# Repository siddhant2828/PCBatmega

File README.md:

PCB atmega328
In this project I have design a customized PCB for arduino board using EAGLE IDE.
The board files , schematic file and PNJ image.

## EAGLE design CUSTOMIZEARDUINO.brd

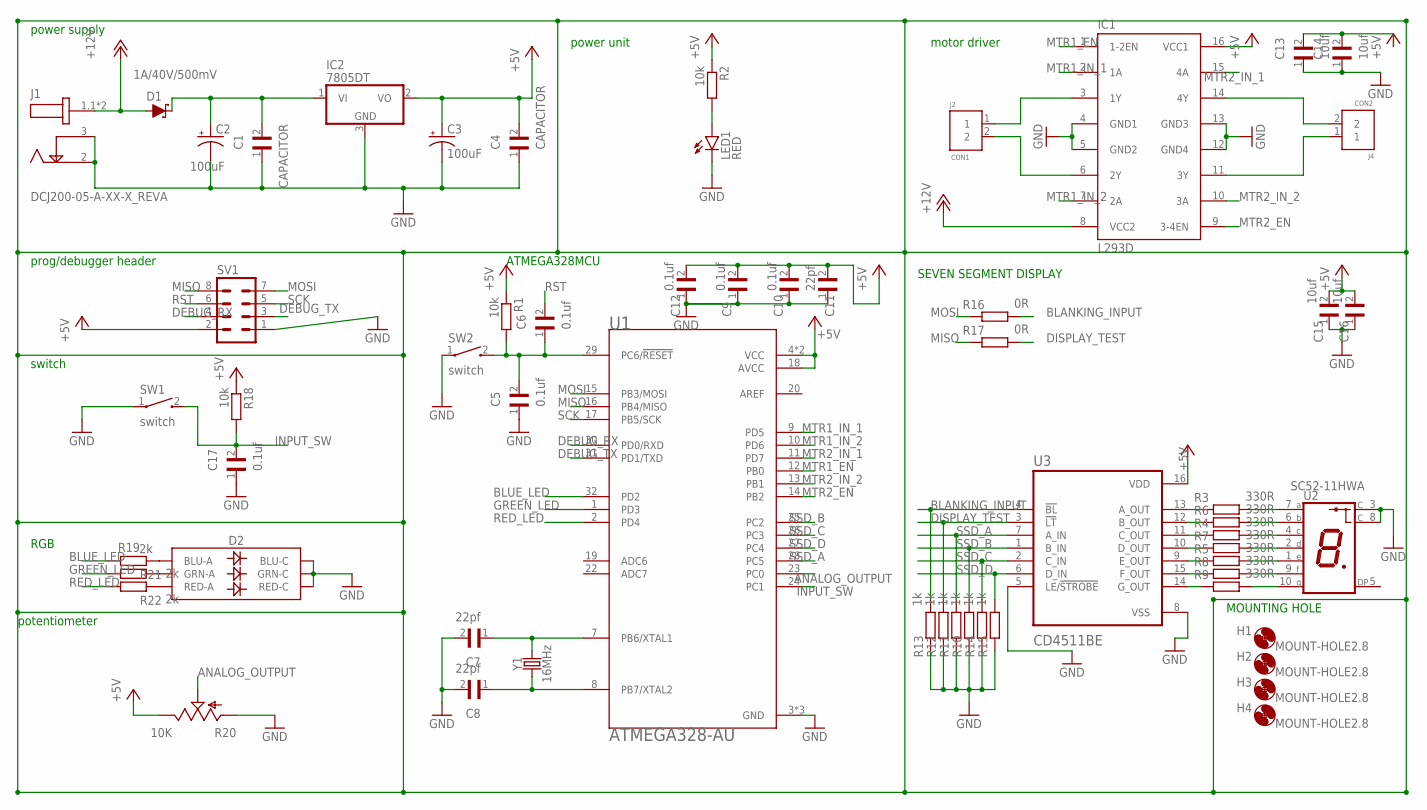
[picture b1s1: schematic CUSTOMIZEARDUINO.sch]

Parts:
C1, C4: CAPACITOR; C0603
C2, C3: 100uF; CPOL-RADIAL-2.5MM-6.5MM
C5, C6, C9, C10, C12, C17: 0.1uf; C0603
C7, C8, C11: 22pf; C0603
C13, C14, C15, C16: 10uf; C0603
D1: 1A/40V/500mV; SMA-DIODE
D2: LED-RGBBRG; LED-TRICOLOR-5050
H1, H2, H3, H4: MOUNT-HOLE2.8; 2,8
IC1: L293D; DIL16
IC2: 7805DT; TO252
J1: DCJ200-05-A-XX-X_REVA; GCT_DCJ200-05-A-XX-X_REVA
J2: CON1; CONN_282836-2
J4: CON2; CONN_282836-2
LED1: RED; SMARTLED-TTW
R1, R2, R18: 10k; R0603
R3, R4, R5, R6, R7, R8, R9: 330R; R0603
R10, R11, R12, R13, R14, R15: 1k; R0603
R16, R17: 0R; R0603
R19, R21, R22: 2k; R0603
R20: 10K; S64W
SV1: MA04-2
SW1, SW2: switch; SW_1437566-3
U1: ATMEGA328-AU; QFP80P900X900X120-32N
U2: SC52-11HWA; LED_SC52-11HWA
U3: CD4511BE; DIP794W45P254L1969H508Q16
Y1: 16MHz; HC49US

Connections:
+5V: C3.1 (+), C4.2, C9.2, C10.2, C11.2, C12.2, C13.2, C14.2, C15.2, C16.2, IC1.16 (VCC1), IC2.2 (VO), R1.1, R2.1, R18.1, R20.E, SV1.2, U1.4 (VCC), U1.6 (VCC), U1.18 (AVCC), U3.16 (VDD)
+12V: D1.A, IC1.8 (VCC2), J1.1.1 (1), J1.1.2 (1)
ANALOG_OUTPUT: R20.S, U1.23 (PC0)
BLANKING_INPUT: R13.2, R16.2, U3.4 (!BL)
BLUE_LED: D2.6 (BLU-A), R19.1, R19.2, U1.32 (PD2)
DEBUG_RX: SV1.4, U1.30 (PD0/RXD)
DEBUG_TX: SV1.3, U1.31 (PD1/TXD)
DISPLAY_TEST: R12.2, R17.2, U3.3 (!LT)
GND: C1.1, C2.2 (-), C3.2 (-), C4.1, C5.1, C7.2, C8.2, C9.1, C10.1, C11.1, C12.1, C13.1, C14.1, C15.1, C16.1, C17.1, D2.1 (BLU-C), D2.2 (RED-C), D2.3 (GRN-C), IC1.4 (GND1), IC1.5 (GND2), IC1.12 (GND4), IC1.13 (GND3), IC2.3 (GND), J1.2, J1.3, LED1.C@1 (C), R10.1, R11.1, R12.1, R13.1, R14.1, R15.1, R20.A, SV1.1, SW1.1, SW2.1, U1.3 (GND), U1.5 (GND), U1.21 (GND), U2.3 (C), U2.8 (C), U3.5 (LE/!STROBE), U3.8 (VSS)
GREEN_LED: R21.1, U1.1 (PD3)
INPUT_SW: C17.2, R18.2, SW1.2, U1.24 (PC1)
MISO: R17.1, SV1.8, U1.16 (PB4/MISO)
MOSI: R16.1, SV1.7, U1.15 (PB3/MOSI)
MTR1_EN: IC1.1 (1-2EN), U1.12 (PB0)
MTR1_IN_1: IC1.2 (1A), U1.9 (PD5)
MTR1_IN_2: IC1.7 (2A), U1.10 (PD6)
MTR2_EN: IC1.9 (3-4EN), U1.14 (PB2)
MTR2_IN_1: IC1.15 (4A), U1.11 (PD7)
MTR2_IN_2: IC1.10 (3A), U1.13 (PB1)
unnamed: C1.2, C2.1 (+), D1.C, IC2.1 (VI)
unnamed: C5.2, C6.1, R1.2, SW2.2, U1.29 (PC6/!RESET)
unnamed: C7.1, U1.7 (PB6/XTAL1), Y1.2
unnamed: C8.1, U1.8 (PB7/XTAL2), Y1.1
unnamed: LED1.A@1 (A), R2.2
unnamed: R3.1, U3.13 (A_OUT)
unnamed: R6.1, U3.12 (B_OUT)
unnamed: R4.1, U3.11 (C_OUT)
unnamed: R7.1, U3.10 (D_OUT)
unnamed: IC1.14 (4Y), J4.2
unnamed: IC1.11 (3Y), J4.1
unnamed: IC1.3 (1Y), J2.1
unnamed: IC1.6 (2Y), J2.2
unnamed: R5.1, U3.9 (E_OUT)
unnamed: R8.1, U3.15 (F_OUT)
unnamed: R9.1, U3.14 (G_OUT)
unnamed: R3.2, U2.7 (A)
unnamed: R6.2, U2.6 (B)
unnamed: R4.2, U2.4 (C)
unnamed: R7.2, U2.2 (D)
unnamed: R5.2, U2.1 (E)
unnamed: R8.2, U2.9 (F)
unnamed: R9.2, U2.10 (G)
unnamed: D2.4 (GRN-A), R21.2
unnamed: D2.5 (RED-A), R22.2
RED_LED: R22.1, U1.2 (PD4)
RST: C6.2, SV1.6
SCK: SV1.5, U1.17 (PB5/SCK)
SSD_A: R11.2, U1.28 (PC5), U3.7 (A_IN)
SSD_B: R10.2, U1.25 (PC2), U3.1 (B_IN)
SSD_C: R14.2, U1.26 (PC3), U3.2 (C_IN)
SSD_D: R15.2, U1.27 (PC4), U3.6 (D_IN)

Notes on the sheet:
power supply
power unit
motor driver
prog/debugger header
switch
RGB
potentiometer
ATMEGA328MCU
SEVEN SEGMENT DISPLAY
MOUNTING HOLE

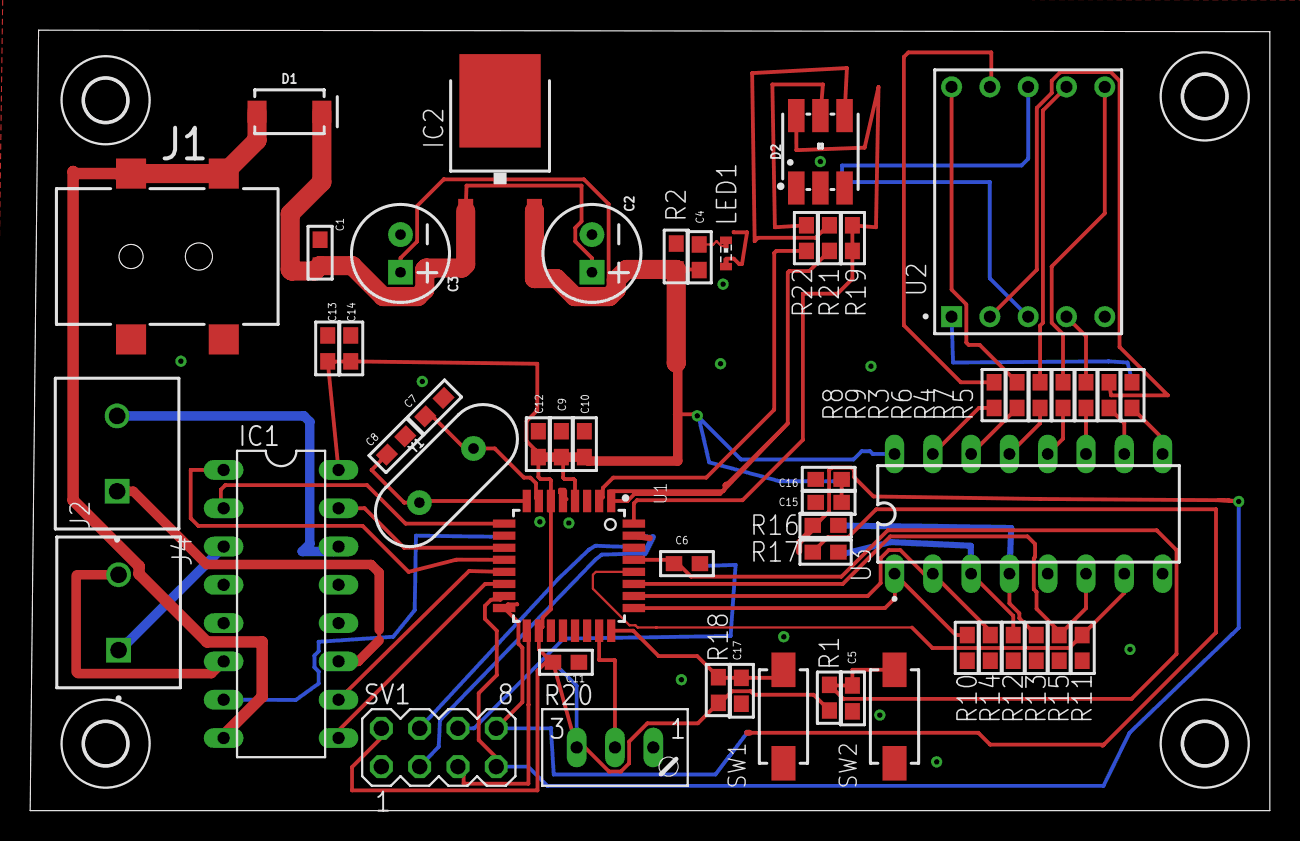
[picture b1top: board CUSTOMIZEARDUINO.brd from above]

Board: 2 copper layers, 82.2 x 51.8 mm, 58 parts (0 on the bottom side), 51 nets.

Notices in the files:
parts and their libraries:
SparkFun-Capacitors: Licensing: Creative Commons ShareAlike 4.0 International - https://creativecommons.org/licenses/by-sa/4.0
